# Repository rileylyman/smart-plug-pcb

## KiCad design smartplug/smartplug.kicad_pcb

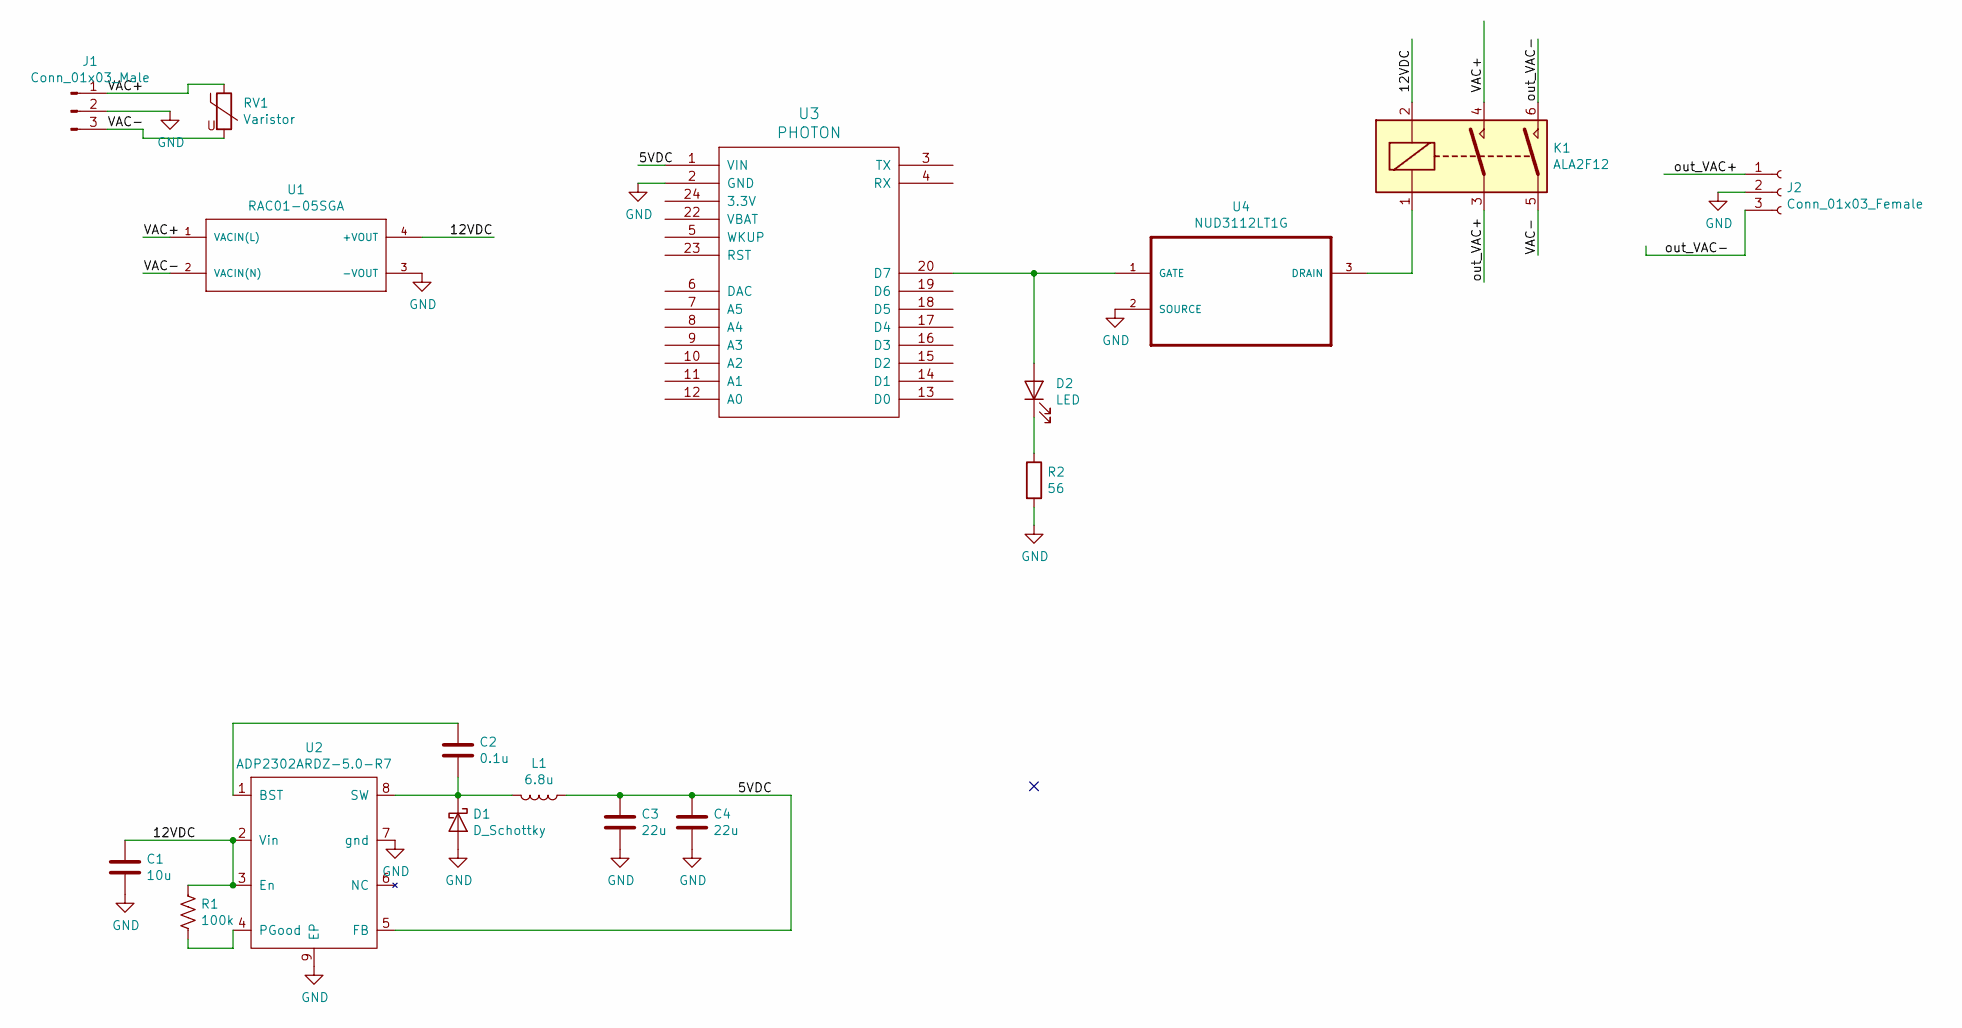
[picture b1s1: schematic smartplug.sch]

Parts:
C1: 10u; C_0805_2012Metric
C2: 0.1u; C_0805_2012Metric
C3, C4: 22u; C_0805_2012Metric
D1: D_Schottky; D_SMB
D2: LED; LED_0603_1608Metric
J1: Conn_01x03_Male; 1985852
J2: Conn_01x03_Female; TE_3-213598-2-new
K1: ALA2F12; ALA2F12-pins_changed
L1: 6.8u; IND_SRR1240-6R8M
R1: 100k; R_0805_2012Metric
R2: 56; R_0805_2012Metric
RV1: Varistor; FUSE_0154004.DR
U1: RAC01-05SGA; CONV_RAC01-05SGA
U2: ADP2302ARDZ-5.0-R7; SOIC127P600X175-9N
U3: PHOTON; photon_smd
U4: NUD3112LT1G; SOT95P240X110-3N

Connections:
/5VDC: C3.1, C4.1, L1.1, U2.5 (FB), U3.1 (VIN)
/12VDC: C1.1, K1.2, R1.1, U1.4 (+VOUT), U2.2 (Vin), U2.3 (En)
/VAC+: J1.1, K1.4, RV1.1, U1.1 (VACIN(L))
/VAC-: J1.3, K1.5, RV1.2, U1.2 (VACIN(N))
/out_VAC+: J2.1, K1.3
/out_VAC-: J2.3, K1.6
GND: C1.2, C3.2, C4.2, D1.2 (A), J1.2, J2.2, R2.2, U1.3 (-VOUT), U2.7 (gnd), U2.9 (EP), U3.2 (GND), U4.2 (SOURCE)
unnamed: C2.1, D1.1 (K), L1.2, U2.8 (SW)
unnamed: C2.2, U2.1 (BST)
unnamed: D2.1 (K), R2.1
unnamed: D2.2 (A), U3.20 (D7), U4.1 (GATE)
unnamed: K1.1, U4.3 (DRAIN)
unnamed: R1.2, U2.4 (PGood)

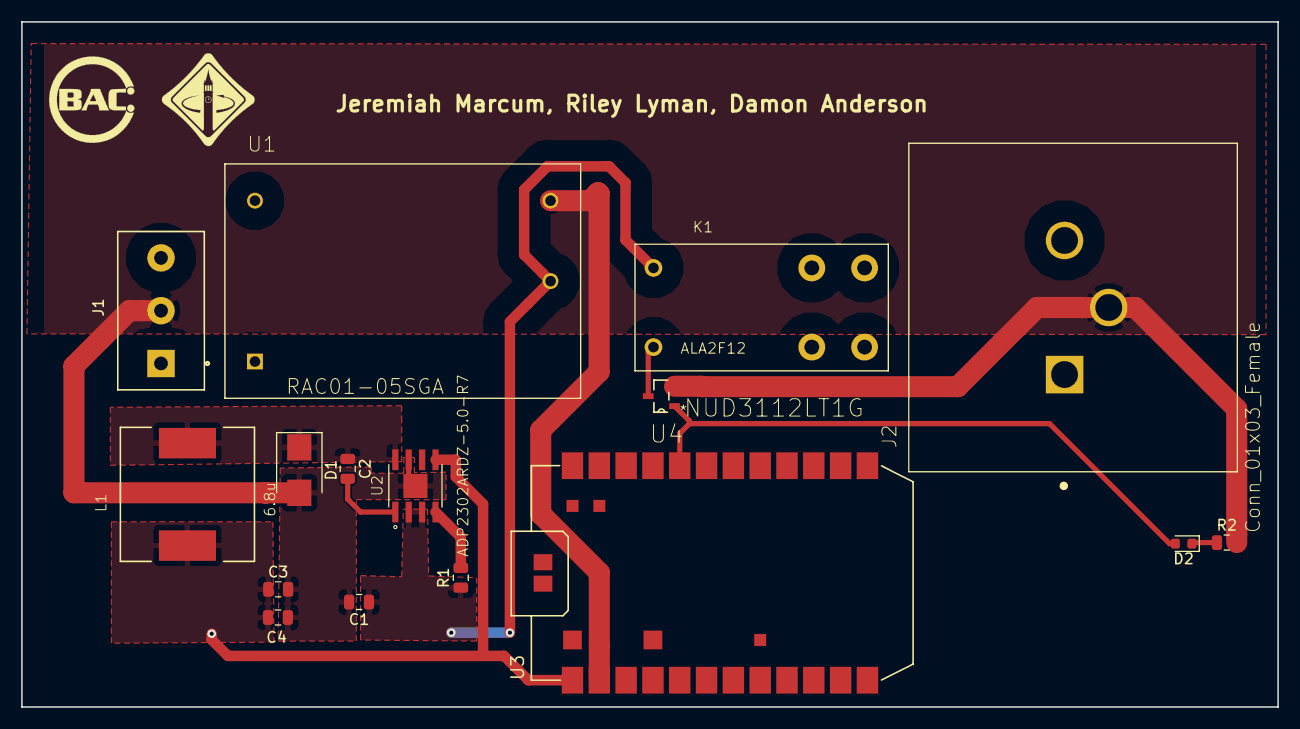
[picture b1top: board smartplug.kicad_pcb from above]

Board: 2 copper layers, 119.0 x 64.9 mm, 17 parts (1 on the bottom side), 13 nets.

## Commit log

2019-03-21 start project and add ac-dc converter lib
2019-03-21 add relay symbol
2019-03-21 Adding Particle schematics and footprints
2019-04-02 Added LED
2019-04-02 Added schematic from usb charger
2019-04-03 added circuit protection
2019-04-03 library fixes and female->male connector
2019-04-03 fix footprint libs
2019-04-03 assign footprints and netlist
2019-04-03 change relay footprint
2019-04-03 added soic footprint
2019-04-03 first draft layout
2019-04-07 added connector footprint and updated PCB
2019-04-07 Fixed clearances and added silkscreen
2019-04-07 pass DFM
2019-04-09 rearranged board to reduce area
